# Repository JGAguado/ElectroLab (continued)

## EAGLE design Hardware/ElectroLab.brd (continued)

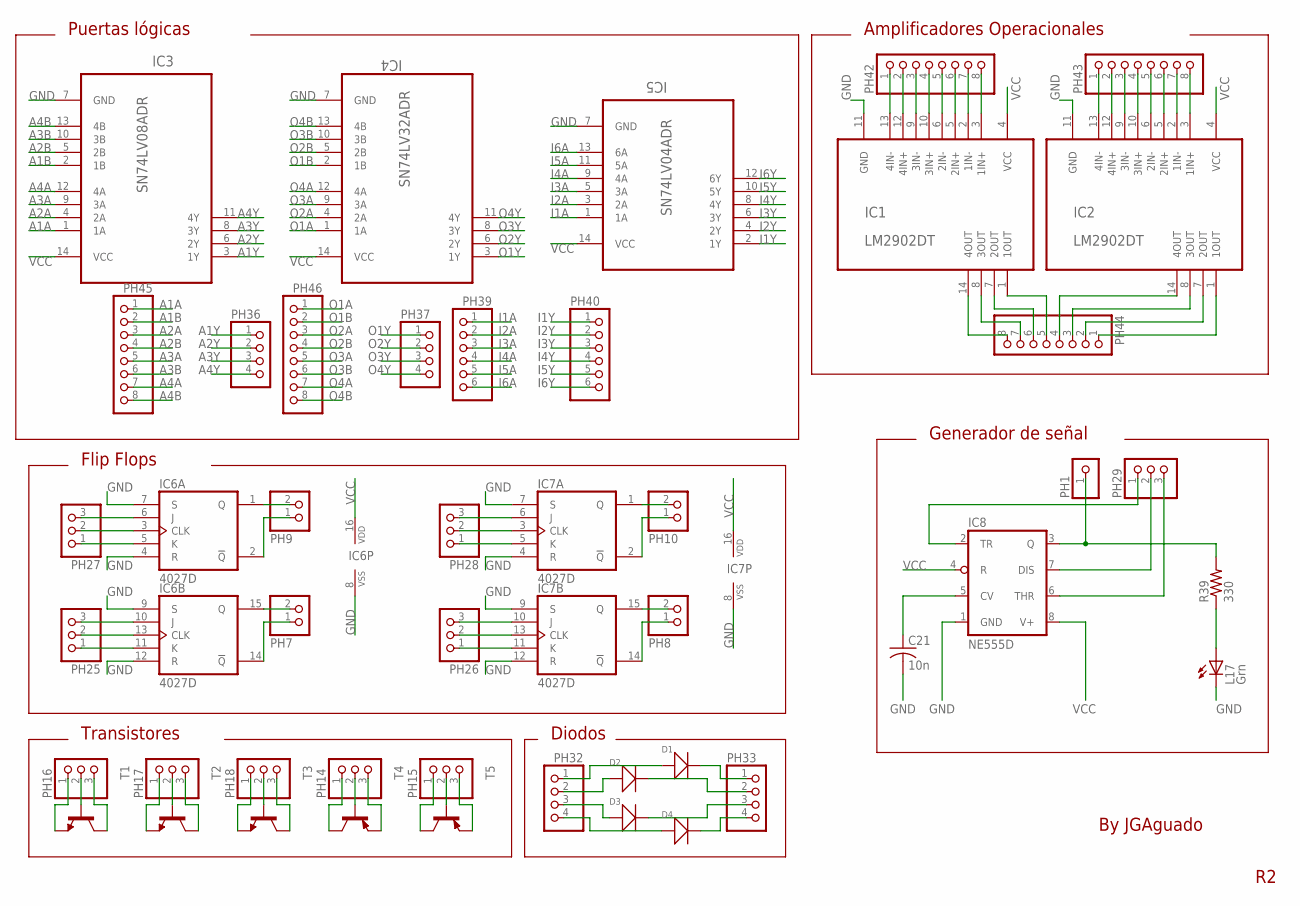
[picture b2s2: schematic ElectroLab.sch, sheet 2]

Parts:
C21: 10n; 0603
D1, D2, D3, D4: SMD-DIODE-SWITCHING-75V-150MA(D1206); LED-1206
IC1, IC2: LM2902DT; SOIC127P600X175-14N
IC3: SN74LV08ADR; SOIC127P600X175-14N
IC4: SN74LV32ADR; SOIC127P600X175-14N
IC5: SN74LV04ADR; SOIC127P600X175-14N
IC6, IC7: 4027D; SO16
IC8: NE555D; SO08
L17: Grn; 1206
PH1: PINHD-1X1; 1X01
PH7, PH8, PH9, PH10: PINHD-1X2; 1X02
PH14, PH15, PH16, PH17, PH18, PH25, PH26, PH27, PH28, PH29: PINHD-1X3; 1X03
PH32, PH33, PH36, PH37: PINHD-1X4; 1X04
PH39, PH40: PINHD-1X6; 1X06
PH42, PH43, PH44, PH45, PH46: PINHD-1X8; 1X08
R39: 330; R1206
T1, T2, T3: BC817-16-NPN-SOT23-BEC; SOT23-BEC
T4, T5: -PNP-SOT23-BCE; SOT23-BCE

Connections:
A1A: IC3.1 (1A), PH45.1; also elsewhere on the board
A1B: IC3.2 (1B), PH45.2; also elsewhere on the board
A1Y: IC3.3 (1Y), PH36.1
A2A: IC3.4 (2A), PH45.3; also elsewhere on the board
A2B: IC3.5 (2B), PH45.4; also elsewhere on the board
A2Y: IC3.6 (2Y), PH36.2
A3A: IC3.9 (3A), PH45.5; also elsewhere on the board
A3B: IC3.10 (3B), PH45.6; also elsewhere on the board
A3Y: IC3.8 (3Y), PH36.3
A4A: IC3.12 (4A), PH45.7; also elsewhere on the board
A4B: IC3.13 (4B), PH45.8; also elsewhere on the board
A4Y: IC3.11 (4Y), PH36.4
GND: C21.2, IC1.11 (GND), IC2.11 (GND), IC3.7 (GND), IC4.7 (GND), IC5.7 (GND), IC6.4 (R), IC6.7 (S), IC6.8 (VSS), IC6.9 (S), IC6.12 (R), IC7.4 (R), IC7.7 (S), IC7.8 (VSS), IC7.9 (S), IC7.12 (R), IC8.1 (GND), L17.C; also elsewhere on the board
I1A: IC5.1 (1A), PH39.1; also elsewhere on the board
I1Y: IC5.2 (1Y), PH40.1
I2A: IC5.3 (2A), PH39.2; also elsewhere on the board
I2Y: IC5.4 (2Y), PH40.2
I3A: IC5.5 (3A), PH39.3; also elsewhere on the board
I3Y: IC5.6 (3Y), PH40.3
I4A: IC5.9 (4A), PH39.4; also elsewhere on the board
I4Y: IC5.8 (4Y), PH40.4
I5A: IC5.11 (5A), PH39.5; also elsewhere on the board
I5Y: IC5.10 (5Y), PH40.5
I6A: IC5.13 (6A), PH39.6; also elsewhere on the board
I6Y: IC5.12 (6Y), PH40.6
unnamed: D4.+, PH32.4
unnamed: D4.-, PH33.4
unnamed: D1.+, PH32.1
unnamed: IC6.1 (Q), PH9.2
unnamed: IC6.15 (Q), PH7.2
unnamed: IC7.1 (Q), PH10.2
unnamed: IC7.15 (Q), PH8.2
unnamed: L17.A, R39.1
unnamed: IC1.13 (4IN-), PH42.1
unnamed: IC1.12 (4IN+), PH42.2
unnamed: IC1.9 (3IN-), PH42.3
unnamed: IC1.10 (3IN+), PH42.4
unnamed: IC1.6 (2IN-), PH42.5
unnamed: IC1.5 (2IN+), PH42.6
unnamed: IC1.2 (1IN-), PH42.7
unnamed: IC1.3 (1IN+), PH42.8
unnamed: IC2.13 (4IN-), PH43.1
unnamed: IC6.5 (K), PH27.1
unnamed: IC6.3 (CLK), PH27.2
unnamed: IC6.6 (J), PH27.3
unnamed: IC6.11 (K), PH25.1
unnamed: IC6.13 (CLK), PH25.2
unnamed: IC6.10 (J), PH25.3
unnamed: IC7.5 (K), PH28.1
unnamed: IC7.3 (CLK), PH28.2
unnamed: IC7.6 (J), PH28.3
unnamed: IC7.11 (K), PH26.1
unnamed: IC7.13 (CLK), PH26.2
unnamed: IC7.10 (J), PH26.3
unnamed: IC6.2 (!Q), PH9.1
unnamed: IC6.14 (!Q), PH7.1
unnamed: IC7.2 (!Q), PH10.1
unnamed: IC7.14 (!Q), PH8.1
unnamed: D3.+, PH32.3
unnamed: D2.+, PH32.2
unnamed: IC2.12 (4IN+), PH43.2
unnamed: IC2.9 (3IN-), PH43.3
unnamed: IC2.10 (3IN+), PH43.4
unnamed: IC2.6 (2IN-), PH43.5
unnamed: IC2.5 (2IN+), PH43.6
unnamed: IC2.2 (1IN-), PH43.7
unnamed: IC2.3 (1IN+), PH43.8
unnamed: IC1.14 (4OUT), PH44.8
unnamed: IC1.8 (3OUT), PH44.7
unnamed: IC1.7 (2OUT), PH44.6
unnamed: IC1.1 (1OUT), PH44.5
unnamed: IC2.14 (4OUT), PH44.4
unnamed: IC2.8 (3OUT), PH44.3
unnamed: D1.-, PH33.1
unnamed: IC2.7 (2OUT), PH44.2
unnamed: IC2.1 (1OUT), PH44.1
unnamed: D2.-, PH33.2
unnamed: D3.-, PH33.3
unnamed: PH16.1, T1.E
unnamed: PH16.2, T1.B
unnamed: PH16.3, T1.C
unnamed: PH17.1, T2.E
unnamed: PH17.2, T2.B
unnamed: PH17.3, T2.C
unnamed: PH18.1, T3.E
unnamed: PH18.2, T3.B
unnamed: PH18.3, T3.C
unnamed: PH14.1, T4.C
unnamed: PH14.2, T4.B
unnamed: PH14.3, T4.E
unnamed: PH15.1, T5.C
unnamed: PH15.2, T5.B
unnamed: PH15.3, T5.E
unnamed: IC8.2 (TR), PH29.1
unnamed: IC8.3 (Q), PH1.1, R39.2
unnamed: C21.1, IC8.5 (CV)
unnamed: IC8.7 (DIS), PH29.2
unnamed: IC8.6 (THR), PH29.3
O1A: IC4.1 (1A), PH46.1; also elsewhere on the board
O1B: IC4.2 (1B), PH46.2; also elsewhere on the board
O1Y: IC4.3 (1Y), PH37.1
O2A: IC4.4 (2A), PH46.3; also elsewhere on the board
O2B: IC4.5 (2B), PH46.4; also elsewhere on the board
O2Y: IC4.6 (2Y), PH37.2
O3A: IC4.9 (3A), PH46.5; also elsewhere on the board
O3B: IC4.10 (3B), PH46.6; also elsewhere on the board
O3Y: IC4.8 (3Y), PH37.3
O4A: IC4.12 (4A), PH46.7; also elsewhere on the board
O4B: IC4.13 (4B), PH46.8; also elsewhere on the board
O4Y: IC4.11 (4Y), PH37.4
VCC: IC1.4 (VCC), IC2.4 (VCC), IC3.14 (VCC), IC4.14 (VCC), IC5.14 (VCC), IC6.16 (VDD), IC7.16 (VDD), IC8.4 (R), IC8.8 (V+); also elsewhere on the board

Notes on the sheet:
Puertas lógicas
Amplificadores Operacionales
Flip Flops
Transistores
Diodos
Generador de señal
By JGAguado

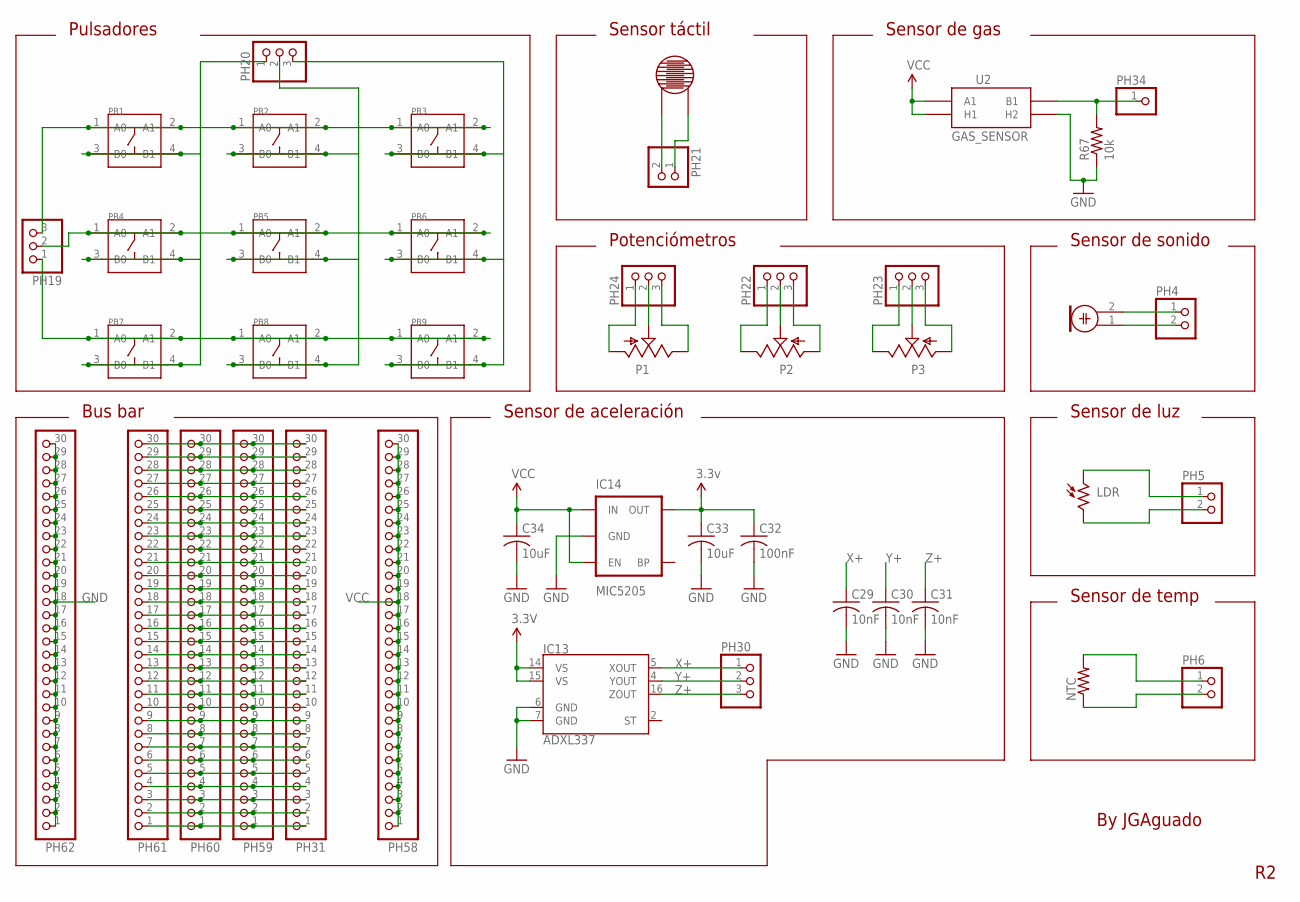
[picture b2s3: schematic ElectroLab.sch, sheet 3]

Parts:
C29, C30, C31: 10nF; 0603
C32: 100nF; 0603
C33, C34: 10uF; 0603
IC13: ADXL337; LFCSP-3X3
IC14: MIC5205; SOT23-5
LDR: V1060_21; TO-5_V10
MIC: ELECTRET_MICROPHON-WM-64PC/64PK; WM-64PC/64PK
NTC: R-US_R1206; R1206@1
P1: SLIDE_POT_20MM
P2, P3: ALPS_RK09K_VERTICAL
PB1, PB2, PB3, PB4, PB5, PB6, PB7, PB8, PB9: SMD-SWITCH-TACTILE-SPST-NO/TS-1109(4P-D6.0MM); SW4-SMD-6.0X6.0X5.0MM
PH4, PH5, PH6, PH21: PINHD-1X2; 1X02
PH19, PH20, PH22, PH23, PH24, PH30: PINHD-1X3; 1X03
PH31, PH58, PH59, PH60, PH61, PH62: PINHD-1X30; 1X30
PH34: PINHD-1X1; 1X01
R67: 10k; 0603
U2: GAS_SENSOR; MQ-3
U$16: RESISTIVE_SENSOR_PAD

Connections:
3.3V: C32.1, C33.1, IC13.14 (VS), IC13.15 (VS), IC14.5 (OUT)
GND: C29.2, C30.2, C31.2, C32.2, C33.2, C34.2, IC13.6 (GND), IC13.7 (GND), IC14.2 (GND), PH62.1, PH62.2, PH62.3, PH62.4, PH62.5, PH62.6, PH62.7, PH62.8, PH62.9, PH62.10, PH62.11, PH62.12, PH62.13, PH62.14, PH62.15, PH62.16, PH62.17, PH62.18, PH62.19, PH62.20, PH62.21, PH62.22, PH62.23, PH62.24, PH62.25, PH62.26, PH62.27, PH62.28, PH62.29, PH62.30, R67.1, U2.HB (H2); also elsewhere on the board
unnamed: PH34.1, R67.2, U2.B1
unnamed: PH21.1, U$16.0
unnamed: PH21.2, U$16.1
unnamed: PH31.7, PH59.7, PH60.7, PH61.7
unnamed: PH31.1, PH59.1, PH60.1, PH61.1
unnamed: PH31.2, PH59.2, PH60.2, PH61.2
unnamed: PH31.3, PH59.3, PH60.3, PH61.3
unnamed: PH31.4, PH59.4, PH60.4, PH61.4
unnamed: PH31.5, PH59.5, PH60.5, PH61.5
unnamed: PH31.6, PH59.6, PH60.6, PH61.6
unnamed: PH31.8, PH59.8, PH60.8, PH61.8
unnamed: PH31.9, PH59.9, PH60.9, PH61.9
unnamed: PH31.10, PH59.10, PH60.10, PH61.10
unnamed: PH31.11, PH59.11, PH60.11, PH61.11
unnamed: PH31.12, PH59.12, PH60.12, PH61.12
unnamed: PH31.13, PH59.13, PH60.13, PH61.13
unnamed: PH31.14, PH59.14, PH60.14, PH61.14
unnamed: PH31.15, PH59.15, PH60.15, PH61.15
unnamed: PH31.16, PH59.16, PH60.16, PH61.16
unnamed: PH31.17, PH59.17, PH60.17, PH61.17
unnamed: PH31.18, PH59.18, PH60.18, PH61.18
unnamed: PH31.19, PH59.19, PH60.19, PH61.19
unnamed: PH31.20, PH59.20, PH60.20, PH61.20
unnamed: PH31.21, PH59.21, PH60.21, PH61.21
unnamed: PH31.22, PH59.22, PH60.22, PH61.22
unnamed: PH31.23, PH59.23, PH60.23, PH61.23
unnamed: PH31.24, PH59.24, PH60.24, PH61.24
unnamed: PH31.25, PH59.25, PH60.25, PH61.25
unnamed: PH31.26, PH59.26, PH60.26, PH61.26
unnamed: PH31.27, PH59.27, PH60.27, PH61.27
unnamed: PH31.28, PH59.28, PH60.28, PH61.28
unnamed: PH31.29, PH59.29, PH60.29, PH61.29
unnamed: PH31.30, PH59.30, PH60.30, PH61.30
unnamed: PB1.1 (A0), PB1.2 (A1), PB2.1 (A0), PB2.2 (A1), PB3.1 (A0), PB3.2 (A1), PH19.3
unnamed: PB4.1 (A0), PB4.2 (A1), PB5.1 (A0), PB5.2 (A1), PB6.1 (A0), PB6.2 (A1), PH19.2
unnamed: PB7.1 (A0), PB7.2 (A1), PB8.1 (A0), PB8.2 (A1), PB9.1 (A0), PB9.2 (A1), PH19.1
unnamed: PB1.3 (B0), PB1.4 (B1), PB4.3 (B0), PB4.4 (B1), PB7.3 (B0), PB7.4 (B1), PH20.1
unnamed: PB2.3 (B0), PB2.4 (B1), PB5.3 (B0), PB5.4 (B1), PB8.3 (B0), PB8.4 (B1), PH20.2
unnamed: PB3.3 (B0), PB3.4 (B1), PB6.3 (B0), PB6.4 (B1), PB9.3 (B0), PB9.4 (B1), PH20.3
unnamed: LDR.1, PH5.1
unnamed: LDR.2, PH5.2
unnamed: NTC.2, PH6.1
unnamed: P2.3, PH22.1
unnamed: P2.2, PH22.2
unnamed: P2.1, PH22.3
unnamed: P1.3, PH24.1
unnamed: P1.2, PH24.2
unnamed: P1.1, PH24.3
unnamed: P3.3, PH23.1
unnamed: P3.2, PH23.2
unnamed: P3.1, PH23.3
unnamed: MIC.2, PH4.1
unnamed: MIC.1, PH4.2
unnamed: NTC.1, PH6.2
VCC: C34.1, IC14.1 (IN), IC14.3 (EN), PH58.1, PH58.2, PH58.3, PH58.4, PH58.5, PH58.6, PH58.7, PH58.8, PH58.9, PH58.10, PH58.11, PH58.12, PH58.13, PH58.14, PH58.15, PH58.16, PH58.17, PH58.18, PH58.19, PH58.20, PH58.21, PH58.22, PH58.23, PH58.24, PH58.25, PH58.26, PH58.27, PH58.28, PH58.29, PH58.30, U2.A1, U2.HA (H1); also elsewhere on the board
X+: C29.1, IC13.5 (XOUT), PH30.1
Y+: C30.1, IC13.4 (YOUT), PH30.2
Z+: C31.1, IC13.16 (ZOUT), PH30.3

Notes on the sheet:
Pulsadores
Potenciómetros
Sensor táctil
Sensor de luz
Sensor de sonido
Sensor de temp
Sensor de aceleración
Bus bar
By JGAguado
Sensor de gas

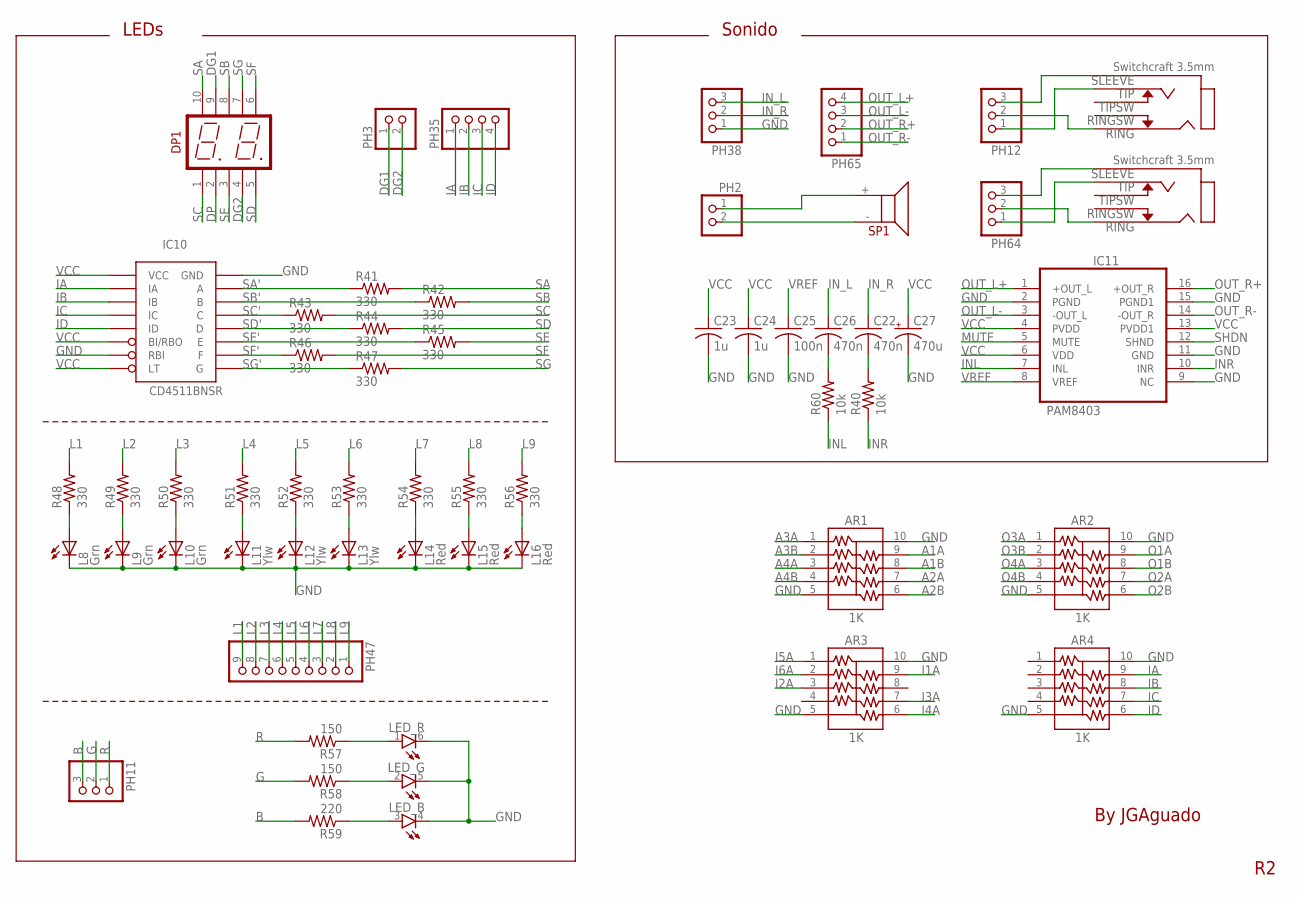
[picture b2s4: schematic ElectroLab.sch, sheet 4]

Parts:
AR1, AR2, AR3, AR4: 1K; RESISTOR_ARRAY_X8_CAY17
C22, C26: 470n; 0603
C23, C24: 1u; 0603
C25: 100n; 0603
C27: 470u; D/7343-31W
DP1: 2X7_SEGMENT_COMMON_CATODE_12_PINS
IC10: CD4511BNSR; SN74LS247D
IC11: PAM8403; SOP-16
JC1, JC2: SWTCHCRFT_3.5JACK5-JACK-SMD; 4-JACK-SMD
L8, L9, L10: Grn; 1206
L11, L12, L13: Ylw; 1206
L14, L15, L16: Red; 1206
LED_: LED_RGB_PLCC-6; PLCC-6
PH2, PH3: PINHD-1X2; 1X02
PH11, PH12, PH38, PH64: PINHD-1X3; 1X03
PH35, PH65: PINHD-1X4; 1X04
PH47: PINHD-1X9; 1X09
R40, R60: 10k; 0603
R41, R42, R43, R44, R45, R46, R47, R48, R49, R50, R51, R52, R53, R54, R55, R56: 330; R1206
R57, R58: 150; R1206
R59: 220; R1206
SP1: 32MM_SPEAKER

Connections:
A1A: AR1.9; also elsewhere on the board
A1B: AR1.8; also elsewhere on the board
A2A: AR1.7; also elsewhere on the board
A2B: AR1.6; also elsewhere on the board
A3A: AR1.1; also elsewhere on the board
A3B: AR1.2; also elsewhere on the board
A4A: AR1.3; also elsewhere on the board
A4B: AR1.4; also elsewhere on the board
B: PH11.3, R59.2
DG1: DP1.9, PH3.1
DG2: DP1.4, PH3.2
DP: DP1.2
GND: AR1.5, AR1.10, AR2.5, AR2.10, AR3.5, AR3.10, AR4.5, AR4.10, C23.2, C24.2, C25.2, C27.-, IC10.GND, IC10.RBI, IC11.2 (PGND), IC11.9 (NC), IC11.11 (GND), IC11.15 (PGND1), L8.C, L9.C, L10.C, L11.C, L12.C, L13.C, L14.C, L15.C, L16.C, LED_.4 (C), LED_.5 (C), LED_.6 (C), PH38.1; also elsewhere on the board
I1A: AR3.9; also elsewhere on the board
I2A: AR3.3; also elsewhere on the board
I3A: AR3.7; also elsewhere on the board
I4A: AR3.6; also elsewhere on the board
I5A: AR3.1; also elsewhere on the board
I6A: AR3.2; also elsewhere on the board
IA: AR4.9, IC10.IA, PH35.1
IB: AR4.8, IC10.IB, PH35.2
IC: AR4.7, IC10.IC, PH35.3
ID: AR4.6, IC10.ID, PH35.4
INL: IC11.7 (INL), R60.1
INR: IC11.10 (INR), R40.1
IN_L: C26.1, PH38.3
IN_R: C22.1, PH38.2
JC1: JC1.2, PH12.2
JC2: JC2.2, PH64.2
L1: PH47.9, R48.2
L2: PH47.8, R49.2
L3: PH47.7, R50.2
L4: PH47.6, R51.2
L5: PH47.5, R52.2
L6: PH47.4, R53.2
L7: PH47.3, R54.2
L8: PH47.2, R55.2
L9: PH47.1, R56.2
MUTE: IC11.5 (MUTE)
unnamed: JC1.3, PH12.1
unnamed: LED_.2 (A), R58.1
unnamed: JC2.1, PH64.3
unnamed: JC2.3, PH64.1
unnamed: C26.2, R60.2
unnamed: C22.2, R40.2
unnamed: PH2.1, SP1.+
unnamed: JC1.1, PH12.3
unnamed: PH2.2, SP1.-
unnamed: L8.A, R48.1
unnamed: L9.A, R49.1
unnamed: L10.A, R50.1
unnamed: L11.A, R51.1
unnamed: L12.A, R52.1
unnamed: L13.A, R53.1
unnamed: L14.A, R54.1
unnamed: L15.A, R55.1
unnamed: L16.A, R56.1
unnamed: LED_.1 (A), R57.1
unnamed: LED_.3 (A), R59.1
O1A: AR2.9; also elsewhere on the board
O1B: AR2.8; also elsewhere on the board
O2A: AR2.7; also elsewhere on the board
O2B: AR2.6; also elsewhere on the board
O3A: AR2.1; also elsewhere on the board
O3B: AR2.2; also elsewhere on the board
O4A: AR2.3; also elsewhere on the board
O4B: AR2.4; also elsewhere on the board
OUT_L+: IC11.1 (+OUT_L), PH65.4
OUT_L-: IC11.3 (-OUT_L), PH65.3
OUT_R+: IC11.16 (+OUT_R), PH65.2
OUT_R-: IC11.14 (-OUT_R), PH65.1
SA: DP1.10, R41.2
SA': IC10.A, R41.1
SB: DP1.8, R42.2
SB': IC10.B, R42.1
SC: DP1.1, R43.2
SC': IC10.C, R43.1
SD: DP1.5, R44.2
SD': IC10.D, R44.1
SE: DP1.3, R45.2
SE': IC10.E, R45.1
SF: DP1.6, R46.2
SF': IC10.F, R46.1
SG: DP1.7, R47.2
SG': IC10.G, R47.1
SHDN: IC11.12 (SHND)
VCC: C23.1, C24.1, C27.+, IC10.BI/RBO, IC10.LT, IC10.VCC, IC11.4 (PVDD), IC11.6 (VDD), IC11.13 (PVDD1); also elsewhere on the board
VREF: C25.1, IC11.8 (VREF)

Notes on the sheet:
Sonido
LEDs
By JGAguado

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
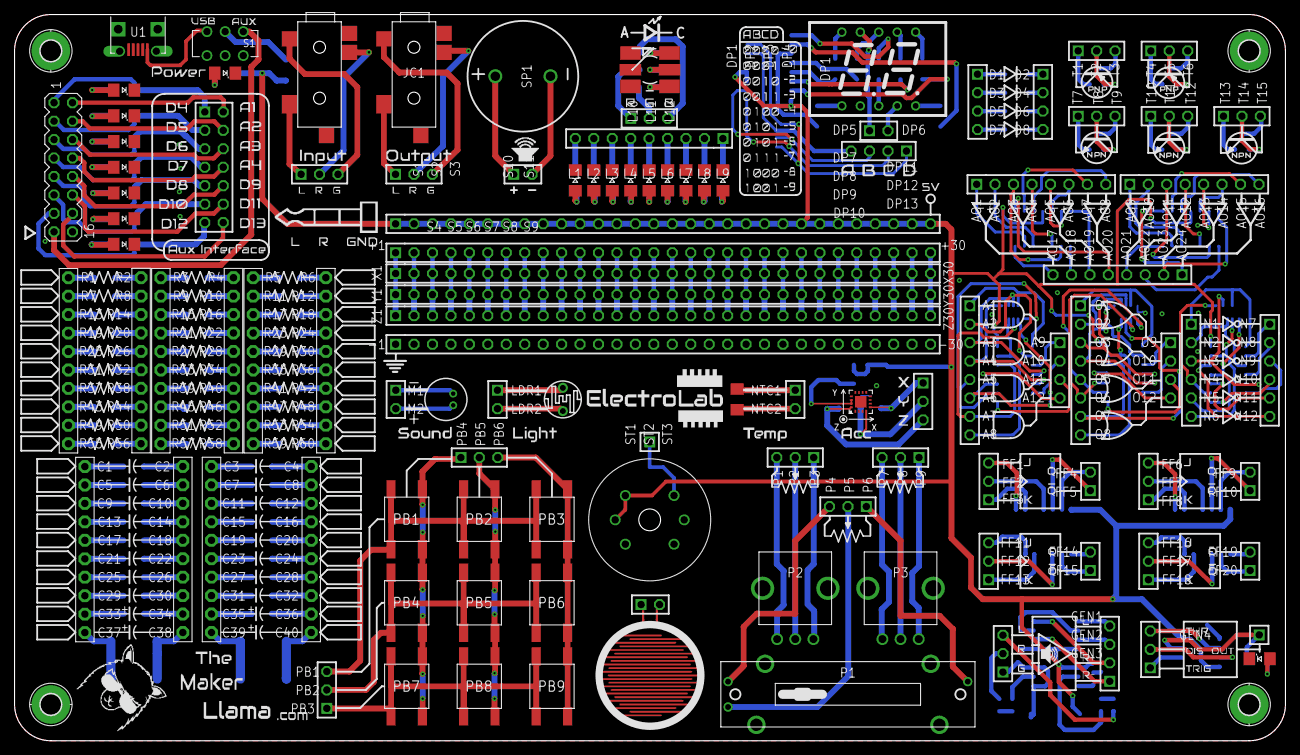
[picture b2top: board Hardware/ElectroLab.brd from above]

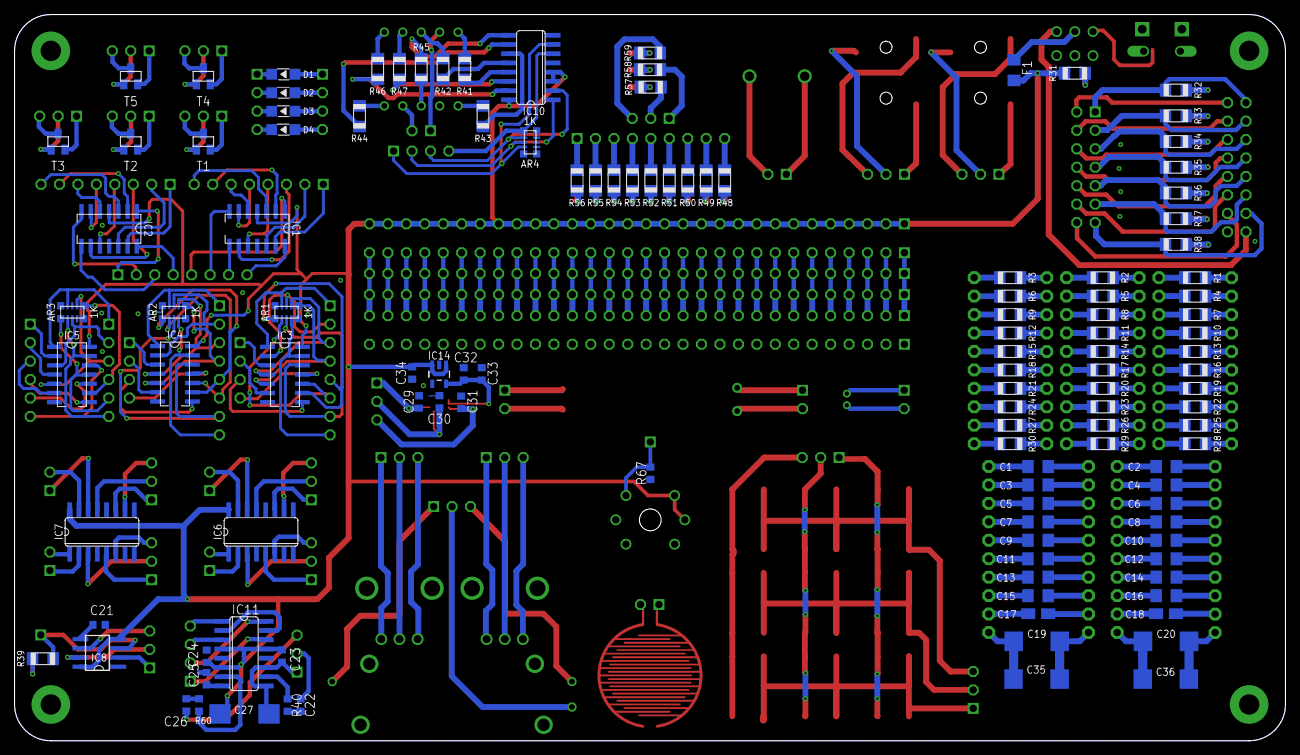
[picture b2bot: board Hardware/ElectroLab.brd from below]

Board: 2 copper layers, 175.0 x 100.0 mm, 232 parts (121 on the bottom side), 357 nets.

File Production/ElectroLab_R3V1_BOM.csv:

No.,part number/description,Package,Value,Qty,RefDefs,Note,Supplier links
1,Resistor,1206,100 Ohm,3,"R1, R2, R3",5% 1/4W ,
2,Resistor,1206,150 Ohm,2,"R57,R58",5% 1/4W ,
3,Resistor,1206,220 Ohm,1,R59,5% 1/4W ,
4,Resistor,1206,330 Ohm,23,"R32 - R38, R41 - R56",5% 1/4W ,
5,Resistor,1206,470 Ohm,4,"R4, R5, R6, R31",5% 1/4W ,
6,Resistor,1206,1 kOhm,3,R7 - R9,5% 1/4W ,
7,Resistor,0603,1 kOhm,3,R61 - R63,5% 1/4W ,
8,Resistor,0603,2 kOhm,3,R64 - R65,5% 1/4W ,
9,Resistor,1206,"4,7 kOhm",3,"R10, R11, R12",5% 1/4W ,
10,Resistor,1206,10 kOhm,7,"R13 - R18, R60",5% 1/4W ,
11,Resistor,0603,10 kOhm,1,R67,,
12,Resistor,1206,15 kOhm,3,"R19, R20, R21",5% 1/4W ,
13,Resistor,1206,47 kOhm,3,"R22, R23, R24",5% 1/4W ,
14,Resistor,1206,100 kOhm,3,"R25, R26, R27",5% 1/4W ,
15,Resistor,0603,100 kOhm,1,R39,5% 1/4W ,
16,Resistor,1206,470 kOhm,3,"R28, R29, R30",5% 1/4W ,
17,Resistor,0603,1 MOhm,1,R40,5% 1/4W ,
18,Bussed Resistor Array,1206,CAY17-102JALF,4,AR1 - AR4,,
19,Capacitor,1206,10 pF,2,"C1, C2",5% 25V,
20,Capacitor,1206,100 pF,2,"C3, C4",5% 25V,
21,Capacitor,1206,1 nF,2,"C5, C6",10% 25V,
22,Capacitor,1206,10 nF,3,"C7, C8, C21",10% 25V,
23,Capacitor,0603,10 nF,4, C28 - C31 ,10% 25V,
24,Capacitor,1206,47 nF,2,"C9, C10",20% 25V,
25,Capacitor,1206,100 nF,3,"C11, C12, C25",20% 25V,
26,Capacitor,0603,100 nF,2,"C22, C32",20% 25V,
27,Capacitor,1206,470 nF,1,C26,20% 25V,
28,Capacitor,1206,1 uF,4,"C13, C14, C23, C24",20% 25V,
29,Capacitor,1206,10 uF,2,"C15, C16",20% 25V,
30,Capacitor,0603,10 uF,2,"C33, C34",20% 25V,
31,Tantalum Capacitor,3216,100 uF,2,"C17, C18",20% >10V,http://www.mouser.es/ProductDetail/Nichicon/UWX1C101MCL1GB/?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
32,Tantalum Capacitor,7343,470 uF,1,C27,20% >10V,http://www.mouser.es/ProductDetail/Nichicon/UCM1A471MCL1GS/?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
33,Tantalum Capacitor,7343,1 mF,2,"C19, C20",20% >10V,http://www.mouser.es/ProductDetail/Nichicon/UWT0J102MNL1GS/?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
34,Cuadruple 2 Input Positive AND Gates,SO-14,SN74LV08ADR,1,IC3,,http://www.mouser.es/ProductDetail/Texas-Instruments/SN74LV0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
35,Cuadruple 2 Input Positive OR Gates,SO-14,SN74LV32ADR,1,IC4,,http://www.mouser.es/ProductDetail/Texas-Instruments/SN74LV3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
36,Hex Inverters,SO-14,SN74LV04ADR,1,IC5,,http://www.mouser.es/ProductDetail/Texas-Instruments/SN74LV0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
37,NPN general purpose transistor,SOT-23,"BC847C,215",3,"T1, T2, T3",,http://www.mouser.es/ProductDetail/NXP-Semiconductors/BC847C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
38,PNP general purpose transistor,SOT-23,"BC857C,215",2,"T4, T5",,http://www.mouser.es/ProductDetail/NXP-Semiconductors/BC857C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
39,Switching Chip Diode,1206,CD1206-S01575,4,"D1, D2, D3, D4",,http://www.mouser.es/ProductDetail/Bourns/CD1206-S01575/?qs=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
40,Low-power quad operational amplifier,SO-14,LM2902DT,3,"IC1, IC2, IC12",,http://www.mouser.es/ProductDetail/STMicroelectronics/LM2902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
41,Precision Timer,SO-8,NE555PSR,1,IC8,,http://www.mouser.es/ProductDetail/Texas-Instruments/NE555PS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
42,Filterless 3w class-d audio amplifier,SOP-16,PAM8403DR,1,IC11,,http://www.mouser.es/ProductDetail/Diodes-Incorporated/PAM84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
43,BCD to 7 segment decoder/driver,SO-16,CD4511BNSR,1,IC10,,http://www.mouser.es/ProductDetail/Texas-Instruments/CD4511B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
44,One channel Toggle-mode Touch sensor IC,SOT23-6,AT42QT1012,1,IC9,,http://www.mouser.es/ProductDetail/Atmel/AT42QT1012-TSHR/?qs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
45,Dual JK flip-flop,SO-16,"HEF4027BT,652",2,"IC6, IC7",,http://www.mouser.es/ProductDetail/NXP-Semiconductors/HEF402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
46,Accelerometer sensor, LFCSP-16 ,ADXL337,1,IC13,,https://www.mouser.at/ProductDetail/Analog-Devices/ADXL337BC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
47,Voltage regulator,SOT23-5,MIC5205,1,IC14,,
48,6x6 mm Pushbutton,SMD,2-1437565-8,9,PB1 - PB9,,http://www.mouser.es/ProductDetail/TE-Connectivity-Alcoswitc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
49,Sub-Miniature Slide Switches,TH,JS202011CQN,1,S1,,http://www.mouser.es/ProductDetail/CK-Components/JS202011CQN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
50,Phone Connectors SMT 3.5MM PHONE JACK,SMD,35RASMT4BHNTRX,1,JC1,,http://www.mouser.es/ProductDetail/Lumex/SML-LX1206IC-TR/?qs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
51,Thermistors - NTC 1206 10Kohm 5%,1206,NC20K00103JBA,1,NTC,,http://www.mouser.es/ProductDetail/Cree-Inc/SLV6A-FKB-CK1P1G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
52,Standard LEDs - SMD 1206 Red,1206,SML-LX1206IC-TR,3,"L14, L15, L16",,
53,Standard LEDs - SMD 1206 Yellow,1206,SML-LX1206YW-TR,10,"L1 - L7, L11, L12, L13",,
54,Standard LEDs - SMD 1206 Green,1206,SML-LX1206GC-TR1,4,"L0, L8, L9, L10",,
55,Standard LEDs - SMD RGB LED,PLCC-6,SLV6A-FKB-CK1P1G1BB7R3R3,1,RGB,,
56,USB Connectors 5P MICRO USB TYPE B,SMD ,10118194-0001LF,1,U1,,
57,"Connector Header 2,54 mm 1 Pos ",TH,1p,1,PH1,,
58,"Connector Header 2,54 mm 2 Pos ",TH,"1*2p 2,54",9,PH2 - PH10,,
59,"Connector Header 2,54 mm 3 Pos ",TH,"1*3p 2,54",20,PH11 - PH30,,
60,"Connector Header 2,54 mm 4 Pos ",TH,"1*4p 2,54",6,"PH31 - PH33, PH35 - PH37",,
61,"Connector Header 2,54 mm 6 Pos ",TH,"1*6p 2,54",3,"PH38, PH39, PH40",,
62,"Connector Header 2,54 mm 14 Pos (2x7)",TH,"2*7p 2,54",1,PH41 ,,
63,"Connector Header 2,54 mm 8 Pos ",TH,"1*8p 2,54",5,PH42 - PH46,,
64,"Connector Header 2,54 mm 9 Pos ",TH,"1*9p 2,54",1,PH47,,
65,"Connector Header 2,54 mm 10 Pos ",TH,"1*10p 2,54",10,PH48 - PH57,,
66,"Connector Header 2,54 mm 30 Pos ",TH,"1*30p 2,54",5,PH58 - PH62,,
67,"Connector Header 2,54 mm 16 Pos (2x8)",TH,"2*8p 2,54",1,PH63,,https://www.digikey.com/products/en?keywords=SBH11-PBPC-D08-RA-BK
68,Photocell,TH,GL5528,1,LDR, SBH11-PBPC-D08-RA-BK ,
69,2x7 segments display,TH,LTD-4708JR ,1,DP1,Common cathode 2x7,https://www.mouser.at/ProductDetail/Lite-On/LTD-4708JR?qs=sG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
70,Electrec Microphone,TH,,1,MIC,CMEJ-0627-42-P,https://www.mouser.at/ProductDetail/CUI-Devices/CMEJ-0627-42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
71,Sliding potentiometer,TH,PTA2043-2015CPB103,1,P1,,https://www.mouser.at/ProductDetail/Bourns/PTA2043-2015CPB10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
72,Rotary potentiometer,TH,RK09K1130081 ,2,"P2, P3",,https://www.mouser.at/ProductDetail/ALPS/RK09K1130081?qs=%2F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
73,Speaker,TH,AST-01708MR-R,1,SP1,,https://www.mouser.at/ProductDetail/PUI-Audio/AST-01708MR-R?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

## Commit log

2017-12-17 Initial Commit
    * Documentation: ElectroLab Top Layout
    * Hardware: SCH and BRD
2017-12-17 New header and image
2019-01-22 IR sensor replaced with ADXL337 analog accelerometer. 5v to 3.3V power supply IC integrated. Analog level shift circuit based on Op. Amps 3.3v to 5V.
2019-01-22 Analogic accelerometer ADXL337 Layout in BRD
2019-01-22 Minor update of ADXL337 layout
2019-01-22 Modified capacitive tactile sensor. Simplified design.
2019-01-22 Mod: Seriegraphy and layout of ArduLab interface. Modified CTI related seriegraphy
2019-05-06 Documentation updated
2020-01-22 Upgraded Electrolitic Capacitors to Tantalum Capacitors (C15-C18, C27)
2020-01-23 Jumpers added to accelerometer outputs to optionally get the raw signal
2020-01-23 Replaced Microphone footprint to fit with CMEJ-0627-42-P
2020-01-23 Renamed the project ElectroLab
2020-02-07 Removed Amplifier after Acc ADXL337
2020-02-07 Updated RGB layout
2020-02-28 Capacitor area update: - Replaced C19 & C20 for 470uF 7343 (2917) Tantalum capacitors - Added C35 & C36 470uF 7343 (2917) in paralel to C19 & C20 for making 940uF combined - Reviewed Name and Values 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
2020-02-28 Added Silkscreen files
2020-03-03 Added Silkscreen/ElectroLab_names.png
2020-03-03 Updated board layout and silkscreen
2020-04-08 Added Production files for R3V1_2
2020-05-10 Update modifications for ElectroLab R2 CTI20 Release
2020-05-13 Updated illustration images.
2020-05-13 Added Documentation for IDs description
2020-05-24 Updated Documentation Illustrations
2020-05-24 Updated BRD with manufactured silkscreen R2
2021-04-05 First R3 version before merging silkscreen layers
2021-05-02 Updated to R3 (Mk.III)
2021-05-02 Updated: * Documentation * Silkscreens
2021-05-02 Updated Documentation/Top.png with values for resistors & capacitors
2022-04-15 Updated structure
2023-04-10 Renders
2023-04-19 docs
2023-05-14 test
2023-08-12 Updated V3R1
2023-08-13 Added circuits
2023-08-15 HTML Circuit generator
2023-08-16 V3 fixed: - USB-C - BCD pinhead - 330 -> 470 Ohm on RED LEDs for orange led bards
2023-08-27 Replaced Jack connector MQ-2 sensor power through main switch
2023-08-27 Set & reset connected to VCC (3.3V) instead of GND
2023-08-28 readme
2023-09-26 Added design files
2023-09-26 Clean files
2023-09-26 Added schematics and top/bottom renders
2023-10-11 Updated Documentation/Images/ElectroLab.png
2023-11-27 Update Crowdin configuration file
2025-05-04 Add GA support
